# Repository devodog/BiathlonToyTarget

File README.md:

# Introduction

Watching the biathlon world cup events on tv and sensing the thrill and
excitement of the athletes skiing and especially the shooting
performance, an idea of making a similar toy shooting range target
arrangement for nerf gun, was born.

So, how to make this toy biathlon shooting range targets that can detect
a nerf gun dart bullet hit?

What technology could be used to register where a nerf gun dart bullet
have hit and what level of precision is needed?

The next thing the toy shooting range target arrangement will need a way
to tell the shooter if she or he has hit the target or not – for the
real biathlon shooting range target, this is done by mechanically
masking / covering the target hit with a white surface, hiding the
targets black surface.

In general, Piezoelectric elements are used to generate / produce sound
waves when a dc voltage is applied to the Piezo element’s terminals –
usually, a high, hearable, frequency sound.

Piezoelectric elements will also accumulate / generate electric charge
flow when exposed to mechanical stress of a certain amount. It is this
effect that can be used to register a nerf gun dart hit on a plane
target surface if the piezo element is mounted on this same target
surface.

Several simple experiments have shown that the signals from the
piezoelectric elements are sufficient for detecting the impulse a nerf
gun dart hit.

The following will describe the electronic and mechanical design for a
Biathlon Toy Target row, emulating the behaviour of the automatic target
hit indicator. Target hit indicator and reset function will be remote
monitored and controlled.

# Target hit indicator

A Nerf-gun dart bullet weighs about 1 g and have a max speed of ~20 m/s.
Guessing that the maximum speed will be some few milli seconds after
“firing” the Nerf-gun and thereafter the Nerf-gun dart bullet speed will
decline rapidly – a function that describe this would be nice.

The speed of the Nerf-gun dart bullet immediately before it hits the
target will determine the power of impact it will cause on the target
plate.

Without doing any advanced analysis of the physics involved, it is easy
to make a similar knock impact on a plane surface as if the same surface
was hit by a nerf gun dart bullet. For example, using a foot long ruler
or a medium size screwdriver, and hitting the plane surface with the end
of the ruler used as a drumstick.

Now, how should the hit sensor piezoelectric element be used? We need to
know more about the electrical characteristics of the piezoelectric
element and to learn about this, we’ll inspect its electrical behaviour
by use of an oscilloscope, when tapping it lightly, for example with end
of a pencil.

## Electrical properties of the piezoelectric element

The piezoelectric element used for this simple test / experiment, was a
1x1x1 cm in size and has two polarized SMD (surface mounted device)
terminals.

Figure : The piezoelectric element soldered to 3x3 cm Vero-board.

As seen in Figure 1, the terminals are connected to two wires, making it
easy to connect to the oscilloscope-probe. The Vero-board is mounted on
a small plywood contour as a 4.5 cm target to imitate a target for nerf
gun dart bullets. The target contour is screwed onto the edge of a board
for mechanical support.

When connected to the oscilloscope probe and taping the target contour
lightly with the one foot ruler, the following pulse train appeared on
the oscilloscope.

Figure 2: Piezo element mount and the pulse train developed by a medium
knock on the mount board.

The signal generated by the piezoelectric element show that it has an
alternating behaviour and for this impact it variates between –200mV and
+200mV. If the physical impact is greater, larger swing can be expected.
Harder impacts can generate up to 4 V peak-to-peak signal. The maximum
swing is not explored.

If the raw output from this piezoelectric element were to be used to
trigger an event, like an interrupt in a microcontroller, this output
signal will certainly challenge any microcontroller General Purpose IO
interface and even cause permanent damage to the interface.  
One trick to avoid this, would be to interconnect a 3v Zener-diode
between the piezoelectric element and the microcontroller GPIO
interface, but then the impact must be quite substantial to excide the
logical threshold for the GPIO interface, and must always be at the same
level of impact. This simple solution is unsuited for a system that
needs to detect a wide range of target hit impacts to allow for various
types of nerf-guns and variable shooting range.

So, to make use of piezoelectric element as target hit sensor, the
output must be refined and amplified, to comply with the requirement of
trigger a wide range of target hit impacts.

## Sensor circuit

Since the piezoelectric element produces an alternating signal, the
signal needs to be rectified and smoothened so that it represents a
single positive pulse. This signal manipulation is usually called “peak
detection”, which is a method to find the highest pulse value among a
series of variable sized pulses.

Figure : Simple peak detector using an Operational Amplifier.

As this piezoelectric signal will need to be amplifies, it is sensible
to use an Operational Amplifier together with the circuit elements (D1,
C2 & R6) that make the peak detector.

Since the microcontrollers GPIO interface in general accepts only
positive voltages and uses 0V as ground reference, it is most practical
to use a single supply Operational Amplifiers and use supply voltage for
the OpAmps suitable for the MCUs GPIOs.

To detect target hit with variable impact, the rectified and smoothened
signal from the piezoelectric element is forwarded to a level
comparator. The comparator will output Vcc if the input signal from the
peak detector is higher than a reference level, and output 0V if the
input signal is lower than this reference level.

Figure : Super simple peak detector followed by a mid-level comparator
to produce a 5V hit trigger/interrupt signal (max outupt is VCC – 1V =
5V according to the data sheet for TL321).

The target hit detector is simple and can be implemented on a small,
printed circuit board, which is easily mounted on the backside of a
piece of 4 to 6 mm plywood, where the frontside of the plywood piece, is
the target to hit.

The impact on the target plate will propagate to the piezoelectric
element soldered onto the PCB, which will produce a single pulse that
can trigger an event on an MCU.

# Detector Hardware solution

The Nerf gun bullet dart hit detector circuit design is manufactured as
a 30x30mm PCB by use of the free CAD tool KiCad. The PCB design
documents are part of the BiathlonToyTargets git repository.

Figure : PCB for the target hit detector. The rightmost uses a surface
mounted piezo element.

# Target hit indication

The shooting range biathlon targets indicate immediately if one is hit,
by covering the black surface that represents the target. To imitate
this functionality, a small servo motor will rotate a circle shaped 3 mm
MDF plate, called the Cover-plate, between the target surface and the
front plate.

Figure : The construction of the biathlon toy target stand.

Figure : The biathlon toy targets with one hit indication - the
rightmost target surface is covered by its cover plate.

## Shooting range biathlon toy targets construction

The biathlon toy targets stand with cover plates for hit indication, is
a simple construction made from 16 mm floorboards of fir tree and a 6 mm
plywood target stand cover with 5 circular formed “windows” exposing the
biathlon toy target surfaces.

From Figure 5, two floorboards form as top end bottom of the
construction, providing support for both the target surface for the nerf
gun dart bullets (the lower floorboard), and for mounting the servo
motors for each hit indicator cover plate. The cover plate is attached
to the servo motors spine shaft by a spine socket fixture to rotate it
to cover the target “window”.

## Servo motor requirements

The servo motor must be able to rotate the target cover, meaning that it
has to provide sufficient torque for this operation. The size and weight
of the target cover determines the necessary torque needed.  
As the biathlon standing target diameter is 11.5 cm, the target cover
must have a slightly larger diameter and a diameter of 13 cm will
probably be a practical size. Alternative materials can be used, but for
the current prototype, 3 mm MDF board will be used. This material’s
density is approximately 820 kg/m<sup>3</sup>, which gives that MDF
target cover described above will weigh approximately …..

Figure 8: Servo motor (<https://www.elefun.no/p/prod.aspx?v=15938>) to
move the target cover. The 6 mm plywood target cover can and will be
replaced with 3 mm MDF material.

The volume of the target cover = d·πr<sup>2</sup> = 0.003 m · π · (0.065
m)<sup>2</sup> = <u>12.68 · 10<sup>-6</sup> m<sup>3</sup></u>

- The total weight of the target cover is approximately **33 grams**.

- Centre of mass relative to servo shaft (13 cm/2 + 1 ∽ **7.5 cm**)

- Required servo torque = 33g \* 7.5 ~ **0,25 kg/cm**

So, using an analogue that outputs a torque of 6.7 kg / cm would
certainly be more than sufficient, which the Power HD-6001HB will do.

## Servo motor control and operation

In general, servo motors are controlled by a 50 Hz PWM signal, usually
provided by a microcontroller. The servo motor’s interface contains of
6V and Ground connection in addition to the PWM signal wire.

# Solution infrastructure

The biathlon toy target solution infrastructure is shown in …

Figure 9: Biathlon toy target hardware infrastructure for automatic hit
detection and indication.

# Wiring plan

Every target will need power and two signal leads. The power will be
distributed from a 6V battery pack onto a power bus that is connected
(some daisy chained) five individual connection panels.

Each of these connection panels will then provide power to both target
sensor elements and the servo motor. The signal leads from the sensor
and to the servo will also be connected this connection panel and wired
to the proper GPIO on the MCU.

Figure : Power and signal distribution.

Important to supply each power connection with an appropriated sized
capacitor for stable power source for the hit sensor circuits.

# Microcontroller considerations

The construction of the prototype Biathlon Toy Targets with automatic
hit detection and indication, will so far need a microcontroller that
has at least 10 General Purposed IO ports for handling the shooting
situation. The Biathlon Toy target system must also have a way of
resetting the target covers, preferable from a distance, in addition to
reading the hit results digitally and forward these to another device or
computer. A possible option for this last requirement could be to use a
simple UART, which is often included in microcontrollers.

## Interrupt driven operation for hit detection

Since there are 5 targets that can be hit in any order, the hit sensor
should trigger on an interrupt that reads the signal status on all
targets simultaneously to determine which has been hit. This
functionality will require that 5 of GPIOs, in the selected MCU, used
for hit-detection, must have the ability to trigger an interrupt based
on a signal level change.

## PWM driver for hit indication

The servo motor will tbd

## Wireless and/or wired communication for reset, collecting results and test functions

The easiest way of implementing a communication channel between the MCU
and a PC is to use the legacy serial port operation, since this is based
on the UART functionality, which is also often found integrated in many
microcontrollers.

Implementing the bi-directional operation of this functionality,
commands can be given from a remote terminal, like reset target covers,
and feedback can be received for both hit results and debugging needs.

# Microcontroller used for the Biathlon Toy Target prototype

The MCU used for the Biathlon Toy Target is a 8-bit mcu Attiny 1634 from
Microchip. This is tiny device with 18 programmable IO pins, 16k flash
memory and 1k random access memory, which is more than sufficient to
implement the necessary software operations for the prototype Biathlon
Toy Targets with automatic hit detection and indication.

## Integrated Development Environment – Atmel Studio 7.0

Programmer and debugger… Atmel Ice

# Remaining work on the prototype.

1)  Arranging all loose wires onto the target structure by use of cable
    clips or glue.

2)  Make passage for the wires in wood structure.

3)  Glue spacer (3 mm MDF) onto the centre of the target cover servo
    mount point…

4)  Clue spacer (4 or 3 mm MDF) onto the centre of the back of the
    target cover for mechanical support it shot at when it covers an
    already hit target.

5)  Make an open panel for mounting power jack for charging the battery
    pack, a toggle switch for power on/off the unit.

6)  Make a Veroboard for connecting the power jack and power switch the
    MCU and battery pack.

7)  Solder a 10µF capacitor to all sensor and servo power distribution
    boards.

8)  Test functionality with a new improved front board centre “clamping”
    (this is to make the front board as straight as possible)

9)  <u>IMPROVEMENT</u>: Use the analogue input to measure the battery
    voltage and show it through a terminal command.

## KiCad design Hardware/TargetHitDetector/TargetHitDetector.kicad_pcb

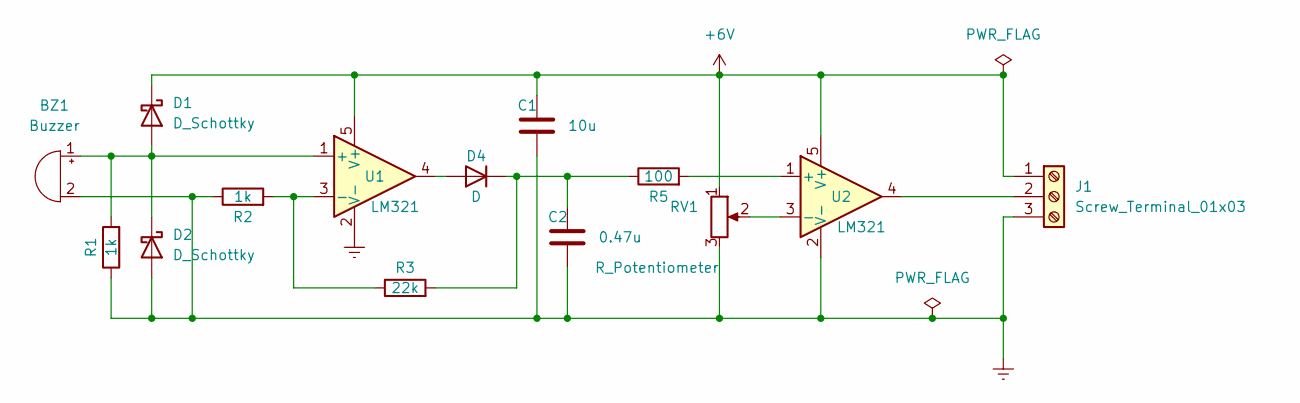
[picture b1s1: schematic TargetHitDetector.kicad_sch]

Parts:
BZ1: Buzzer; Buzzer_Murata_PKMCS0909E
C1: 10u; C_1206_3216Metric_Pad1.33x1.80mm_HandSolder
C2: 0.47u; C_1206_3216Metric_Pad1.33x1.80mm_HandSolder
D1, D2: D_Schottky; D_SOD-523
D4: D; D_1206_3216Metric_Pad1.42x1.75mm_HandSolder
J1: Screw_Terminal_01x03; Wago_734-133_1x03_P3.50mm_Vertical
R1, R2: 1k; R_1206_3216Metric_Pad1.30x1.75mm_HandSolder
R3: 22k; R_1206_3216Metric_Pad1.30x1.75mm_HandSolder
R5: 100; R_1206_3216Metric_Pad1.30x1.75mm_HandSolder
RV1: R_Potentiometer; Potentiometer_ACP_CA9-H5_Horizontal
U1, U2: LM321; SOT-23-5

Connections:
+6V: C1.1, D1.1 (K), J1.1, RV1.1, U1.5 (V+), U2.5 (V+)
Earth: BZ1.2 (+), C1.2, C2.2, D2.2 (A), J1.3, R1.1, R2.1, RV1.3, U1.2 (V-), U2.2 (V-)
unnamed: BZ1.1 (-), D1.2 (A), D2.1 (K), R1.2, U1.1 (+)
unnamed: C2.1, D4.1 (K), R3.2, R5.1
unnamed: D4.2 (A), U1.4
unnamed: J1.2, U2.4
unnamed: R2.2, R3.1, U1.3 (-)
unnamed: R5.2, U2.1 (+)
unnamed: RV1.2, U2.3 (-)

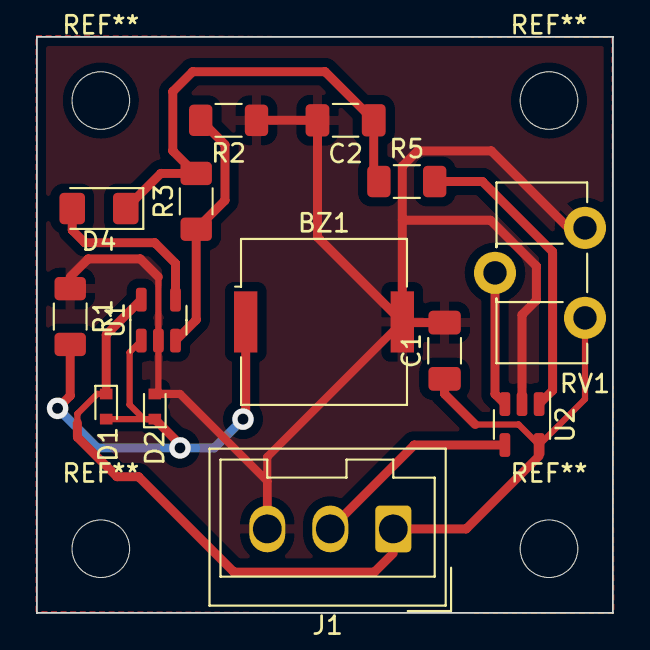
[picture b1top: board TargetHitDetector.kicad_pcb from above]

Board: 2 copper layers, 32.0 x 32.0 mm, 14 parts (0 on the bottom side), 9 nets.

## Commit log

2023-08-07 Including initial some 2D and 3D models
2023-08-07 Hardware and software included in this repository
2023-08-11 Description update
2023-08-14 Converted the word doc description to README markdown doc
2023-08-14 word doc description update -
2024-11-15 Hi-detector hardware design is currently moved.
2024-11-15 Added 3D models and python script directory (for game run).
